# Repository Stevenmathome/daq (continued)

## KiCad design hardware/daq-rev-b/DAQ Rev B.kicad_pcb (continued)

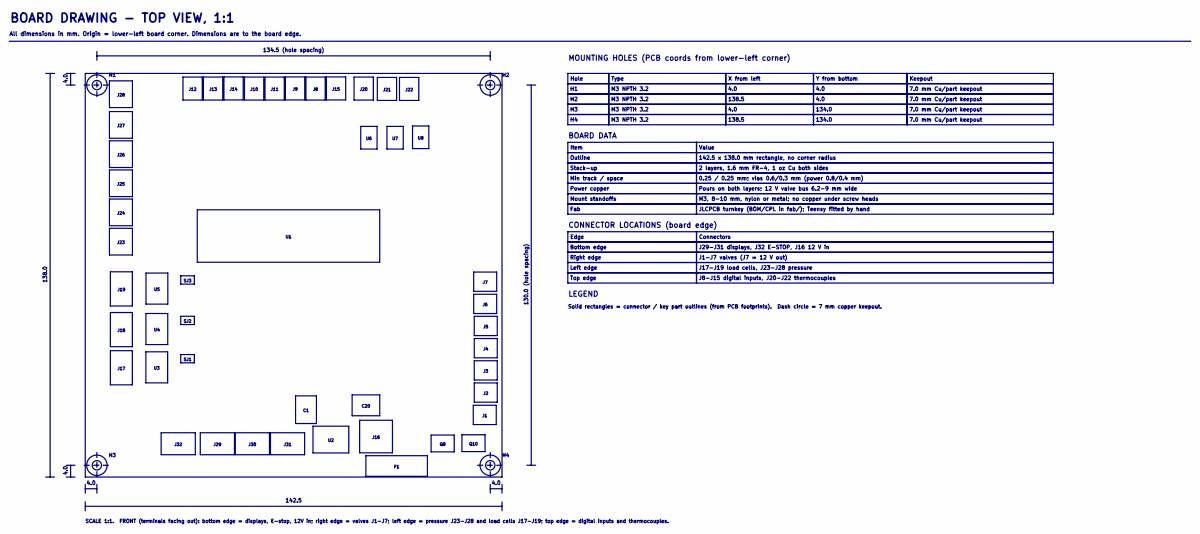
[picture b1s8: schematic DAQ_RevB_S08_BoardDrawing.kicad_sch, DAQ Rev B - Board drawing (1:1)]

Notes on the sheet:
BOARD DRAWING - TOP VIEW, 1:1
All dimensions in mm. Origin = lower-left board corner. Dimensions are to the board edge.
SJ2
J28
J22
J31
J10
Q10
J18
J15
SJ1
J23
J17
C20
J29
J24
J26
J11
J19
J32
J16
J21
J12
J27
J14
J20
SJ3
J25
J13
J30
142.5
138.0
134.5 (hole spacing)
130.0 (hole spacing)
4.0
SCALE 1:1. FRONT (terminals facing out): bottom edge = displays, E-stop, 12V in; right edge = valves J1-J7; left edge = pressure J23-J28 and load cells J17-J19; top edge = digital inputs and thermocouples.
MOUNTING HOLES (PCB coords from lower-left corner)
Hole
Type
X from left

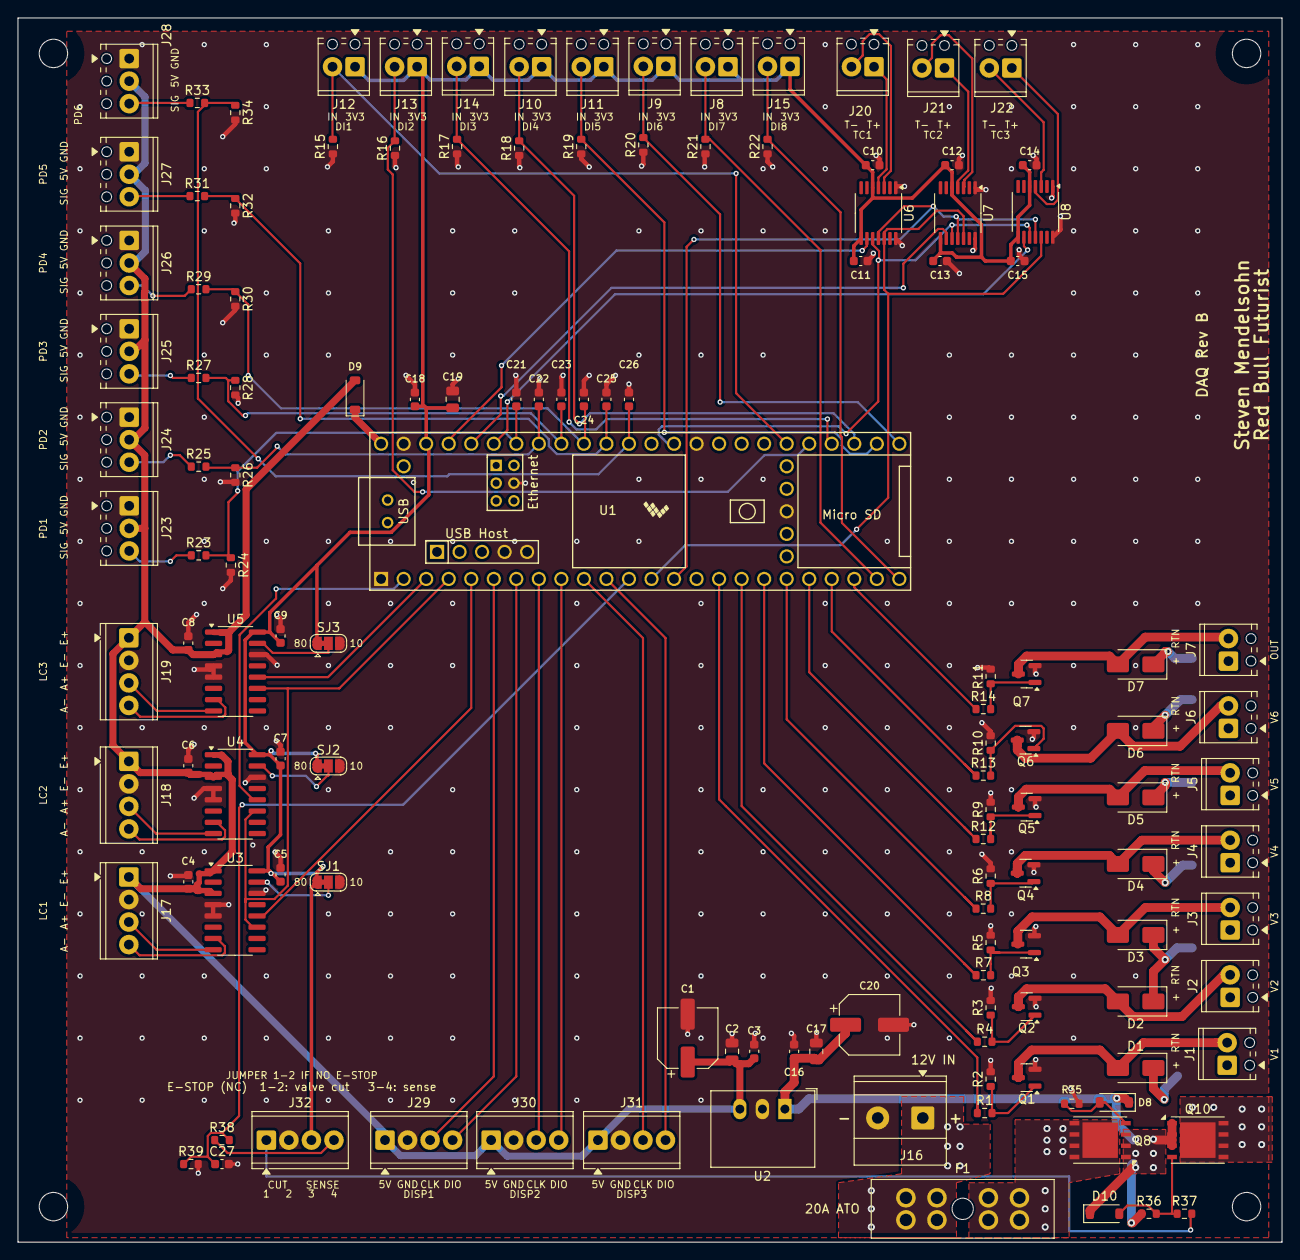
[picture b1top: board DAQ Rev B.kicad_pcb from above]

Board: 2 copper layers, 142.5 x 138.0 mm, 133 parts (0 on the bottom side), 85 nets.

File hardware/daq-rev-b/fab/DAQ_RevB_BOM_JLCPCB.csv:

Comment,Designator,Footprint,LCSC
100uF 25V,"C1,C20",CP_Elec_6.3x7.7,C4747965
10uF 25V,"C2,C17,C19",C_0805_2012Metric,C15850
100nF,"C3,C4,C5,C6,C7,C8,C9,C10,C11,C12,C13,C14,C15,C16,C18,C21,C22,C23,C24,C25,C26,C27",C_0603_1608Metric,C14663
"M7 (1N4007, SMA)","D1,D2,D3,D4,D5,D6,D7",D_SMA,C95872
BZT52C15,"D8,D10",D_SOD-123,C2104
B5819W,D9,D_SOD-123,C8598
"ATO/ATC blade fuse holder (20 A ATO fuse, user supplied)",F1,FuseHolder_Blade_ATO_Littelfuse_FLR_178.6165,C207061
1725656 Phoenix MPT 2.54mm terminal,"J1,J2,J3,J4,J5,J6,J7,J8,J9,J10,J11,J12,J13,J14,J15,J20,J21,J22","TerminalBlock_Phoenix_MPT-0,5-2-2.54_1x02_P2.54mm_Horizontal",C3029316
KF128-5.08-2P-AA 5.08mm terminal block 24A,J16,"TerminalBlock_Phoenix_MKDS-1,5-2-5.08_1x02_P5.08mm_Horizontal",C474952
1725672 Phoenix MPT 2.54mm terminal,"J17,J18,J19,J29,J30,J31,J32","TerminalBlock_Phoenix_MPT-0,5-4-2.54_1x04_P2.54mm_Horizontal",C3816889
1725669 Phoenix MPT 2.54mm terminal,"J23,J24,J25,J26,J27,J28","TerminalBlock_Phoenix_MPT-0,5-3-2.54_1x03_P2.54mm_Horizontal",C5288763
AO3400A,"Q1,Q2,Q3,Q4,Q5,Q6,Q7",SOT-23,C20917
AON6407,"Q8,Q10",DFN-8-1EP_6x5mm_P1.27mm_EP4x4mm,C7603355
1k,"R1,R4,R7,R8,R12,R13,R14,R38",R_0603_1608Metric,C21190
10k,"R2,R3,R5,R6,R9,R10,R11,R15,R16,R17,R18,R19,R20,R21,R22,R23,R25,R27,R29,R31,R33,R37,R39",R_0603_1608Metric,C25804
20k,"R24,R26,R28,R30,R32,R34",R_0603_1608Metric,C4184
100k,"R35,R36",R_0603_1608Metric,C25803
R-78E5.0-1.0,U2,Converter_DCDC_RECOM_R-78E-0.5_THT,C22371890
HX711,"U3,U4,U5",SOIC-16_3.9x9.9mm_P1.27mm,C43656
MAX31856,"U6,U7,U8",TSSOP-14_4.4x5mm_P0.65mm,C116632

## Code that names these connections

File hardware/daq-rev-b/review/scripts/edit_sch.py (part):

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            if p in points: out.append(s)
    return out

# ---------- 2. J16 pin1: +12V -> VIN_RAW ----------
j16p1=pp[('J16','1')][0]; net=reach(j16p1)
ps=power_syms_at(net,'+12V'); assert len(ps)==1, ps
at=find1(ps[0],'at'); e.remove(ps[0]); label('VIN_RAW',float(at[1]),float(at[2]))
# ---------- 3. Teensy VIN: +5V -> TEENSY_VIN ----------
vin=pp[('U1','48')][0]; net=reach(vin)
ps=power_syms_at(net,'+5V'); assert len(ps)==1, ps
at=find1(ps[0],'at'); e.remove(ps[0]); label('TEENSY_VIN',float(at[1]),float(at[2]))
for t in find(e,'text'):
    if 'NEVER HAVE 12VDC' in str(t[1]):
        t[1]=Q('Teensy VIN fed from +5V through Schottky D9. CUT the VIN-VUSB pad on the Teensy (PJRC) so USB and 12V can both be connected.')
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for l in find(e,'label'):
    if str(l[1])=='LoadCell_DO':
        a=find1(l,'at'); l[1]=Q(dmap[(float(a[1]),float(a[2]))])
for pin,name in (('2','LoadCell2_DO'),('3','LoadCell3_DO')):   # Teensy pad2 = GPIO0, pad3 = GPIO1
    x,y=pp[('U1',pin)][0]; label(name,x,y,180)
# ---------- 5. Teensy extra GND pins ----------
for pin in ('34','47'):
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X0=365.76
# 12V input: J16 -> F1 -> Q8 (P-FET reverse polarity) -> +12V
p=place('Device:Polyfuse','F1','5A hold PTC',X0,40.64,fp=PARTS['PTC5A'][0],fields={'LCSC':'C910846','MPN':'BSMD2920-500-16V','Manufacturer':'BHFUSE'})
label('VIN_RAW',*p['1']); label('VIN_FUSED',*p['2'])
q=place('DAQ_RevB:AO4407A','Q8','AO4407A',388.62,40.64,fp=PARTS['AO4407A'][0],fields={'LCSC':'C2841482','MPN':'AO4407A','Manufacturer':'UMW'})
label('VIN_FUSED',*q['5']); power('+12V',*q['1']); label('PFET_G',*q['4'],180)
z=place('Device:D_Zener','D8','BZT52C15',408.94,40.64,fp=PARTS['BZT52C15'][0],fields={'LCSC':'C2104','MPN':'BZT52C15','Manufacturer':'JSCJ'})
power('+12V',*z['1']); label('PFET_G',*z['2'])
r=place('Device:R','R35','100k',375.92,58.42,fp=PARTS['R100k'][0],fields={'LCSC':'C25803','MPN':'0603WAF1003T5E','Manufacturer':'UNI-ROYAL'})
label('PFET_G',*r['1']); power('GND',*r['2'])
c=place('Device:C_Polarized','C20','100uF 25V',391.16,58.42,fp=PARTS['C100u'][0],fields={'LCSC':'C4747965','MPN':'RST100UF25V006','Manufacturer':'KNSCHA'})
power('+12V',*c['1']); power('GND',*c['2']); CAPMAP['C20']='12V_BULK'
fx=404.0
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flag(fx+8,55.88); power('GND',fx+8,55.88+0)  # GND flag
# Teensy VIN Schottky
d=place('Device:D_Schottky','D9','B5819W',383.54,76.2,fp=PARTS['B5819W'][0],fields={'LCSC':'C8598','MPN':'B5819W SL','Manufacturer':'JSCJ'})
label('TEENSY_VIN',*d['1']); power('+5V',*d['2'])
flag(400.05,76.2); label('TEENSY_VIN',400.05,76.2)
# decoupling caps grid
caps=[('C4','+5V','U3'),('C5','+3V3','U3'),('C6','+5V','U4'),('C7','+3V3','U4'),('C8','+5V','U5'),('C9','+3V3','U5'),
      ('C10','+3V3','U6'),('C11','+3V3','U6'),('C12','+3V3','U7'),('C13','+3V3','U7'),('C14','+3V3','U8'),('C15','+3V3','U8'),
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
